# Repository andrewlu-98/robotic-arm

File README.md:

# 6-Axis Robotic Arm (Work in Progress)

An open-source, 6-DOF robotic arm featuring a custom mixed-architecture control board. The system offloads inverse kinematics (ROS 2 / Python) from a host laptop to an onboard Raspberry Pi Pico W analyzing encoder data and generating step signals.

---

## Hardware Overview

### Mechanical
The physical structure consists of a custom 3D printed robotic arm with one meter span. Joints are driven with Nema stepper motors through gear ratios and pulleys, controlling rotation and movement of arm. Motors are to be guided through sensor inputs (limit switches, MT6701) and controlled via Nema Stepper Motors and precise gear ratios.

### Electrical
Electronics consist of a power supply unit (connected to a wall outlet) sent to a PCB that actively controls the robotic arm through signals to the stepper motors and data from encoders and limit switches mounted near the stepper motors on the physical arm.

The printed circuit board handles logic shifting via 74HCT245, limit switch & encoder monitoring, and I2C multiplexing. It houses pin headers for reusability of all boards in case of PCB failure. The board has thermal reliefs on 24V power pours, decoupling, and pull-up resistors for limit switch activation.

---

## System Architecture

### Hardware Stack
*   **Microcontroller:** Raspberry Pi Pico W (RP2040)
*   **Power:** Mean Well LRS-200-24 (24V, 8.8A), DFR0831 Buck Converter (24V to 5V logic)
*   **Actuators:** 
    *   3x STEPPERONLINE Short Body NEMA 17 (Driven via A4988)
    *   1x Leadshine 42CME06 Closed-Loop (Driven via TMC2209)
    *   2x Leadshine iCL57-23 (Integrated Drivers)
*   **Feedback:** MT6701 Magnetic Encoders (I2C) & Leadshine Quadrature Encoders

### Software Stack (In Progress)
*   **Host (Laptop):** ROS 2, Python, MoveIt 2 (Inverse Kinematics, Trajectory Planning, URDF/Xacro modeling).
*   **Firmware (Pico W):** C++ (Pico SDK). 
    *   **Core 0:** Serial communication (micro-ROS/Custom protocol) & Emergency Stop hardware interrupts.
    *   **Core 1:** PID closed-loop feedback processing.
    *   **PIO:** Mathematically precise step/direction pulse generation for 6 axes.

---

## Development Roadmap

- [x] Mechanical Design and Manufacturing
- [x] PCB Design and Manufacturing
- [x] Finalize BOM and Sourcing
- [x] **[Current]** ROS 2 URDF, RViz2, and Gazebo simulation
- [ ] C++ Firmware: Step generation, and analyzing encoder data
- [ ] Communication between laptop and Pico (micro-ROS)
- [ ] Full integration of mechanical, electrical, and software components

---

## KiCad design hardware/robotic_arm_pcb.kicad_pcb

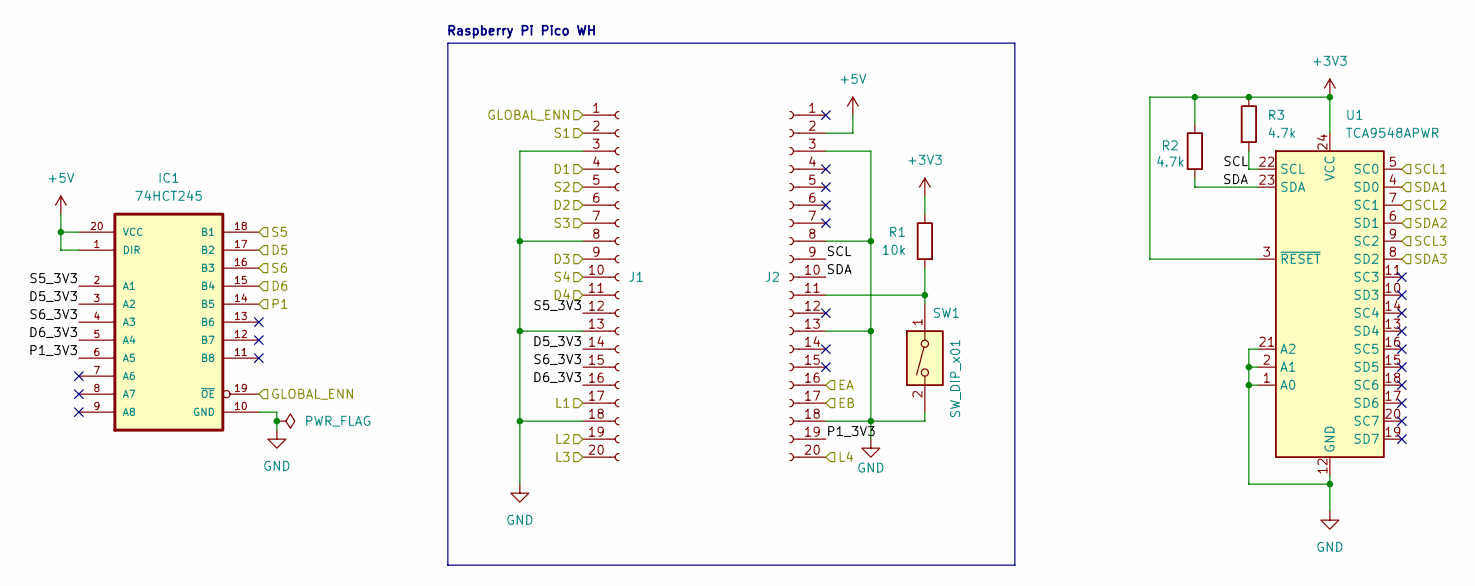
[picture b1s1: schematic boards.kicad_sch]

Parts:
IC1: 74HCT245; MODULE_SN74HCT245N; LCSC C133640
J1, J2: Conn_01x20_Socket; PinSocket_1x20_P2.54mm_Vertical; LCSC C2905423
R1: 10k; R_0805_2012Metric; LCSC C17414
R2, R3: 4.7k; R_0805_2012Metric; LCSC C441984
SW1: SW_DIP_x01; SW_DIP_SPSTx01_Slide_9.78x4.72mm_W7.62mm_P2.54mm; LCSC C501524
U1: TCA9548APWR; TSSOP-24_4.4x7.8mm_P0.65mm; LCSC C130026

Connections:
+3V3: R1.1, R2.1, R3.1, U1.3 (~RESET), U1.24 (VCC); also elsewhere on the board
+5V: IC1.1 (DIR), IC1.20 (VCC), J2.2; also elsewhere on the board
/Boards/D1: J1.4; also elsewhere on the board
/Boards/D2: J1.6; also elsewhere on the board
/Boards/D3: J1.9; also elsewhere on the board
/Boards/D4: J1.11; also elsewhere on the board
/Boards/D5: IC1.17 (B2); also elsewhere on the board
/Boards/D5_3V3: IC1.3 (A2), J1.14
/Boards/D6: IC1.15 (B4); also elsewhere on the board
/Boards/D6_3V3: IC1.5 (A4), J1.16
/Boards/EA: J2.16; also elsewhere on the board
/Boards/EB: J2.17; also elsewhere on the board
/Boards/GLOBAL_ENN: IC1.19 (~OE), J1.1; also elsewhere on the board
/Boards/L1: J1.17; also elsewhere on the board
/Boards/L2: J1.19; also elsewhere on the board
/Boards/L3: J1.20; also elsewhere on the board
/Boards/L4: J2.20; also elsewhere on the board
/Boards/P1: IC1.14 (B5); also elsewhere on the board
/Boards/P1_3V3: IC1.6 (A5), J2.19
/Boards/S1: J1.2; also elsewhere on the board
/Boards/S2: J1.5; also elsewhere on the board
/Boards/S3: J1.7; also elsewhere on the board
/Boards/S4: J1.10; also elsewhere on the board
/Boards/S5: IC1.18 (B1); also elsewhere on the board
/Boards/S5_3V3: IC1.2 (A1), J1.12
/Boards/S6: IC1.16 (B3); also elsewhere on the board
/Boards/S6_3V3: IC1.4 (A3), J1.15
/Boards/SCL: J2.9, R3.2, U1.22 (SCL)
/Boards/SCL1: U1.5 (SC0); also elsewhere on the board
/Boards/SCL2: U1.7 (SC1); also elsewhere on the board
/Boards/SCL3: U1.9 (SC2); also elsewhere on the board
/Boards/SDA: J2.10, R2.2, U1.23 (SDA)
/Boards/SDA1: U1.4 (SD0); also elsewhere on the board
/Boards/SDA2: U1.6 (SD1); also elsewhere on the board
/Boards/SDA3: U1.8 (SD2); also elsewhere on the board
GND: IC1.10 (GND), J1.3, J1.8, J1.13, J1.18, J2.3, J2.8, J2.13, J2.18, SW1.2, U1.1 (A0), U1.2 (A1), U1.12 (GND), U1.21 (A2); also elsewhere on the board
unnamed: J2.11, R1.2, SW1.1

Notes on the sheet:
Raspberry Pi Pico WH

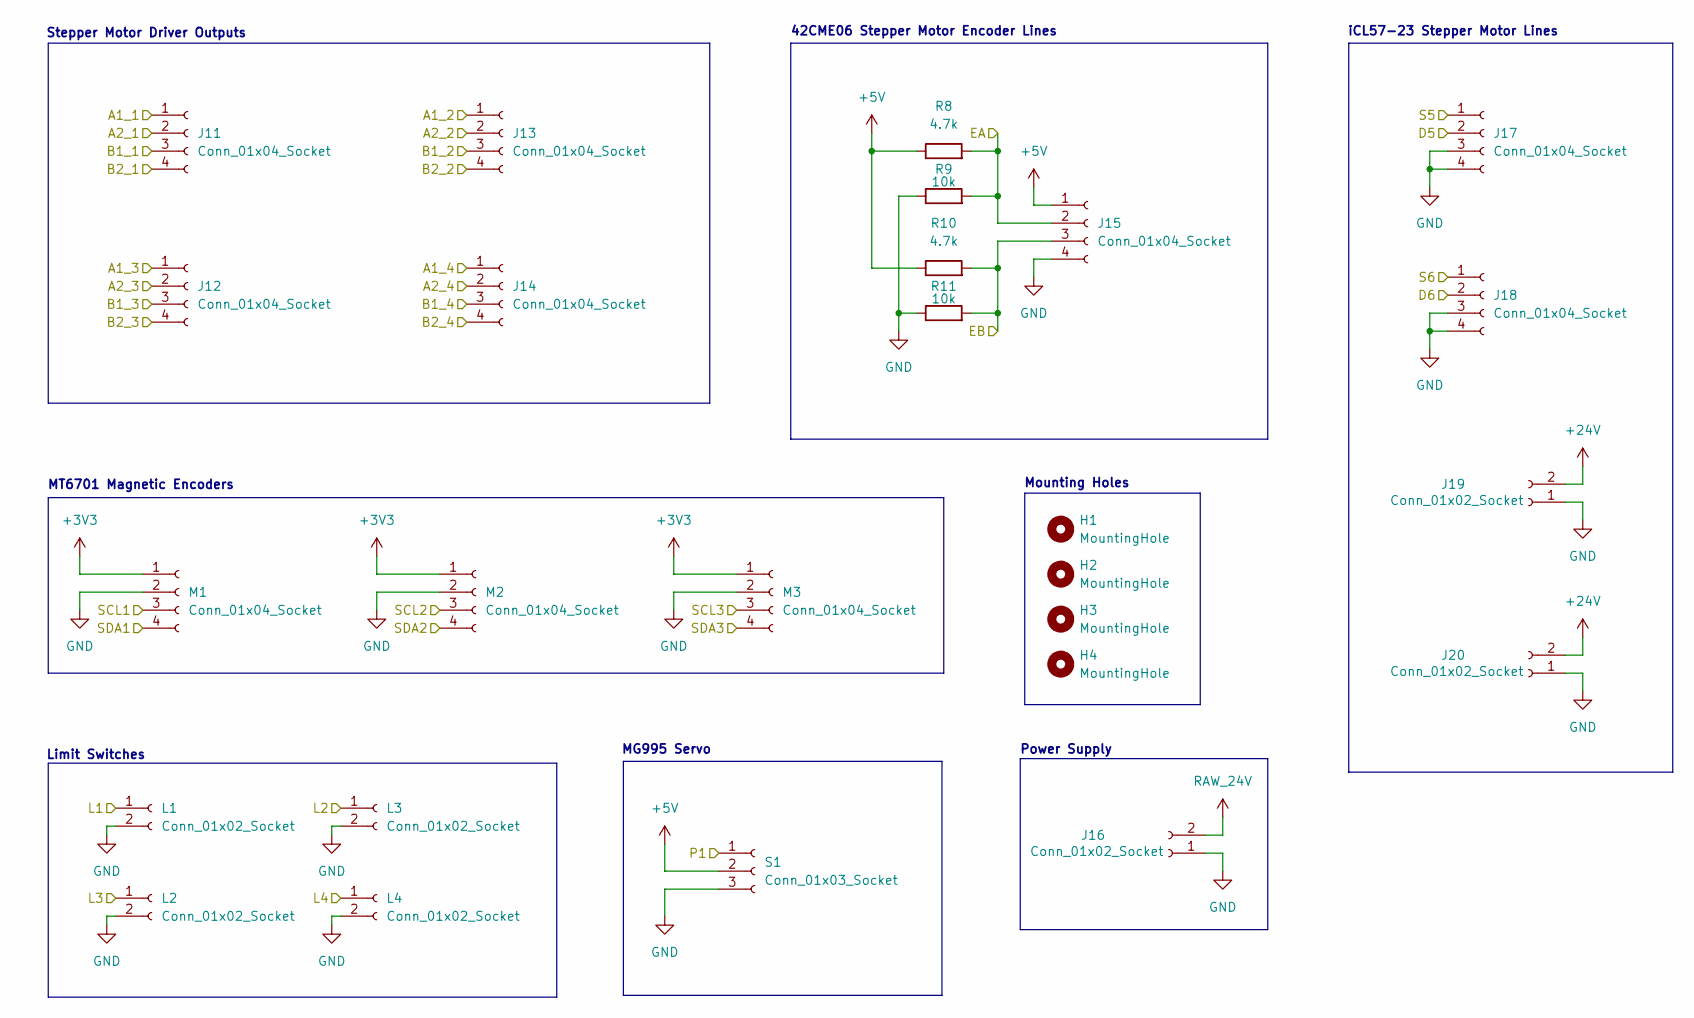
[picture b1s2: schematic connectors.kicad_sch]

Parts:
H1, H2, H3, H4: MountingHole; MountingHole_3.2mm_M3
J11, J12, J13, J14: Conn_01x04_Socket; TerminalBlock_Phoenix_MKDS-1,5-4-5.08_1x04_P5.08mm_Horizont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; LCSC C90087
J15, J17, J18: Conn_01x04_Socket; PinSocket_1x04_P2.54mm_Vertical; LCSC C2718488
J16, J19, J20: Conn_01x02_Socket; TerminalBlock_Phoenix_MKDS-1,5-2-5.08_1x02_P5.08mm_Horizont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; LCSC C474950
L1, L2, L3, L4: Conn_01x02_Socket; PinSocket_1x02_P2.54mm_Vertical; LCSC C49661
M1, M2, M3: Conn_01x04_Socket; PinSocket_1x04_P2.54mm_Vertical; LCSC C2718488
R8, R10: 4.7k; R_0805_2012Metric; LCSC C441984
R9, R11: 10k; R_0805_2012Metric; LCSC C17414
S1: Conn_01x03_Socket; PinSocket_1x03_P2.54mm_Vertical; LCSC C146243

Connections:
+3V3: M1.1, M2.1, M3.1; also elsewhere on the board
+5V: J15.1, R8.1, R10.1, S1.2; also elsewhere on the board
+24V: J19.2, J20.2; also elsewhere on the board
/Boards/D5: J17.2; also elsewhere on the board
/Boards/D6: J18.2; also elsewhere on the board
/Boards/EA: J15.2, R8.2, R9.2; also elsewhere on the board
/Boards/EB: J15.3, R10.2, R11.2; also elsewhere on the board
/Boards/L1: L1.1; also elsewhere on the board
/Boards/L2: L3.1; also elsewhere on the board
/Boards/L3: L2.1; also elsewhere on the board
/Boards/L4: L4.1; also elsewhere on the board
/Boards/P1: S1.1; also elsewhere on the board
/Boards/S5: J17.1; also elsewhere on the board
/Boards/S6: J18.1; also elsewhere on the board
/Boards/SCL1: M1.3; also elsewhere on the board
/Boards/SCL2: M2.3; also elsewhere on the board
/Boards/SCL3: M3.3; also elsewhere on the board
/Boards/SDA1: M1.4; also elsewhere on the board
/Boards/SDA2: M2.4; also elsewhere on the board
/Boards/SDA3: M3.4; also elsewhere on the board
/Connectors/A1_1: J11.1; also elsewhere on the board
/Connectors/A1_2: J13.1; also elsewhere on the board
/Connectors/A1_3: J12.1; also elsewhere on the board
/Connectors/A1_4: J14.1; also elsewhere on the board
/Connectors/A2_1: J11.2; also elsewhere on the board
/Connectors/A2_2: J13.2; also elsewhere on the board
/Connectors/A2_3: J12.2; also elsewhere on the board
/Connectors/A2_4: J14.2; also elsewhere on the board
/Connectors/B1_1: J11.3; also elsewhere on the board
/Connectors/B1_2: J13.3; also elsewhere on the board
/Connectors/B1_3: J12.3; also elsewhere on the board
/Connectors/B1_4: J14.3; also elsewhere on the board
/Connectors/B2_1: J11.4; also elsewhere on the board
/Connectors/B2_2: J13.4; also elsewhere on the board
/Connectors/B2_3: J12.4; also elsewhere on the board
/Connectors/B2_4: J14.4; also elsewhere on the board
GND: J15.4, J16.1, J17.3, J17.4, J18.3, J18.4, J19.1, J20.1, L1.2, L2.2, L3.2, L4.2, M1.2, M2.2, M3.2, R9.1, R11.1, S1.3; also elsewhere on the board
RAW_24V: J16.2; also elsewhere on the board

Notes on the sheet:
Stepper Motor Driver Outputs
Limit Switches
42CME06 Stepper Motor Encoder Lines
Power Supply
iCL57-23 Stepper Motor Lines
MG995 Servo
Mounting Holes
MT6701 Magnetic Encoders

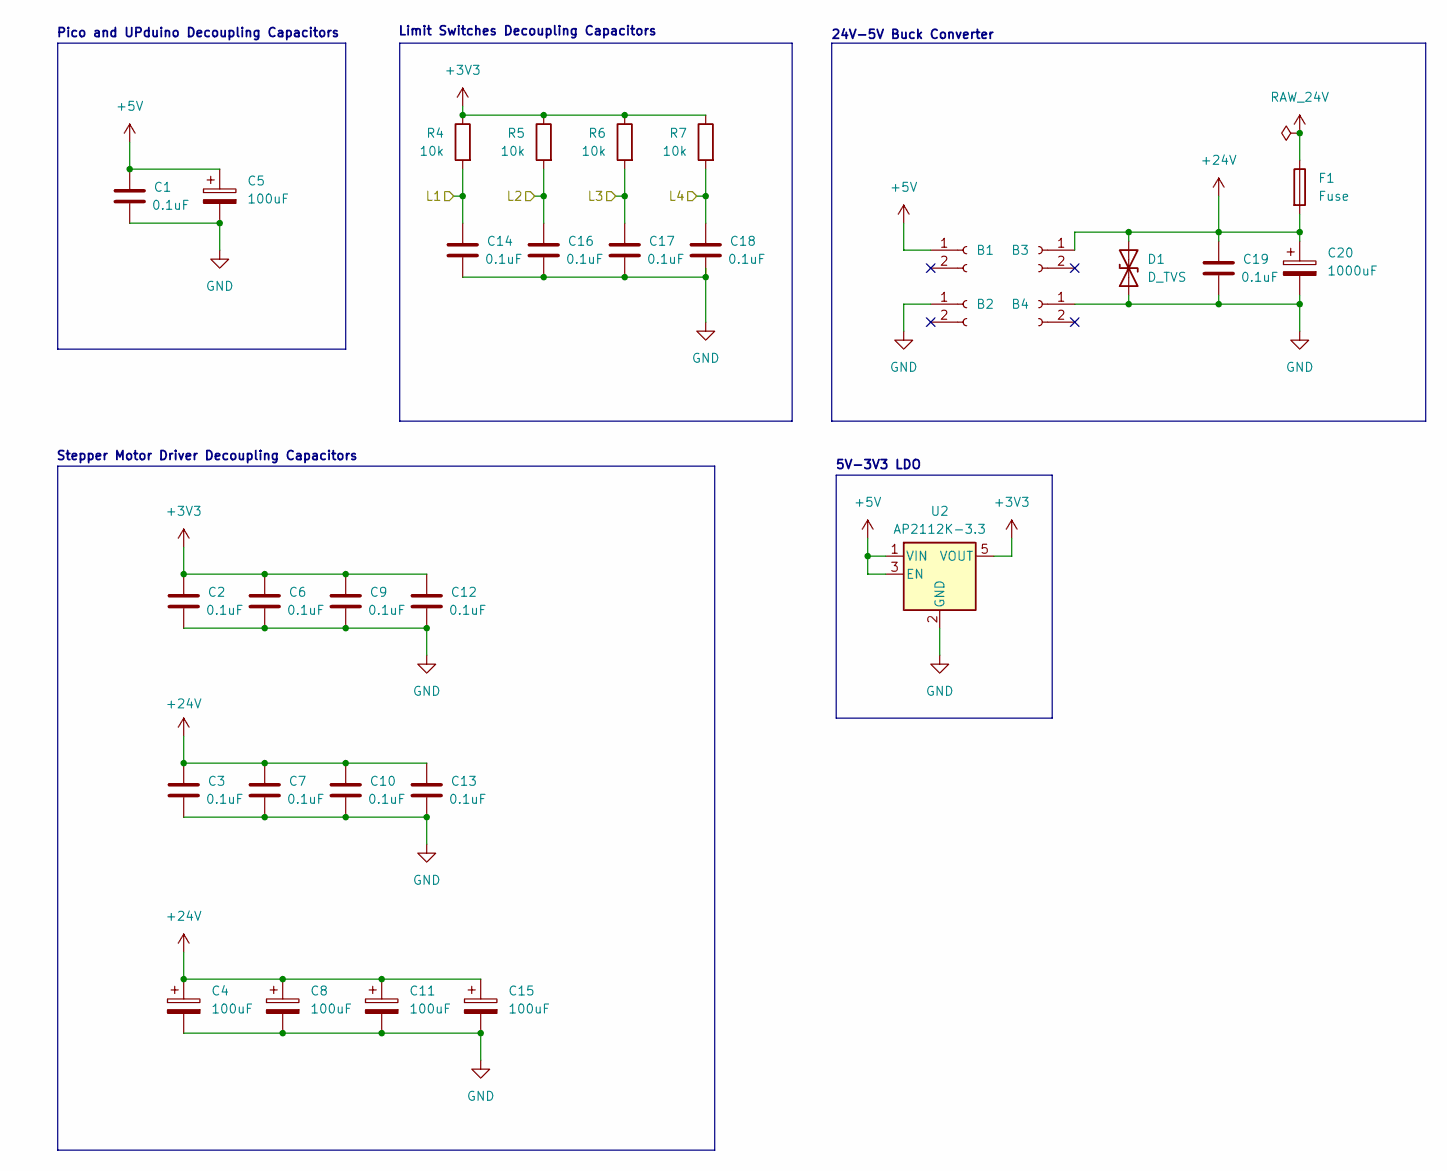
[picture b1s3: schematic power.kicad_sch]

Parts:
B1, B2, B3, B4: Conn_01x02_Socket; PinSocket_1x02_P2.54mm_Vertical; LCSC C49661
C1, C2, C3, C6, C7, C9, C10, C12, C13, C14, C16, C17, C18, C19: 0.1uF; C_0805_2012Metric; LCSC C49678
C4, C5, C8, C11, C15: 100uF; CP_Radial_D6.3mm_P2.50mm; LCSC C2749
C20: 1000uF; CP_Radial_D12.5mm_P5.00mm; LCSC C88743
D1: D_TVS; D_SMB; LCSC C123820
F1: Fuse; Fuseholder_Cylinder-5x20mm_Schurter_0031_8201_Horizontal_Op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; LCSC C3204125
R4, R5, R6, R7: 10k; R_0805_2012Metric; LCSC C17414
U2: AP2112K-3.3; SOT-23-5; LCSC C51118

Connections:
+3V3: C2.1, C6.1, C9.1, C12.1, R4.1, R5.1, R6.1, R7.1, U2.5 (VOUT); also elsewhere on the board
+5V: B1.1 (Pin_1_1), C1.1, C5.1, U2.1 (VIN), U2.3 (EN); also elsewhere on the board
+24V: B3.1 (Pin_1_1), C3.1, C4.1, C7.1, C8.1, C10.1, C11.1, C13.1, C15.1, C19.1, C20.1, D1.2 (A2), F1.2; also elsewhere on the board
/Boards/L1: C14.1, R4.2; also elsewhere on the board
/Boards/L2: C16.1, R5.2; also elsewhere on the board
/Boards/L3: C17.1, R6.2; also elsewhere on the board
/Boards/L4: C18.1, R7.2; also elsewhere on the board
GND: B2.1 (Pin_1_1), B4.1 (Pin_1_1), C1.2, C2.2, C3.2, C4.2, C5.2, C6.2, C7.2, C8.2, C9.2, C10.2, C11.2, C12.2, C13.2, C14.2, C15.2, C16.2, C17.2, C18.2, C19.2, C20.2, D1.1 (A1), U2.2 (GND); also elsewhere on the board
RAW_24V: F1.1; also elsewhere on the board

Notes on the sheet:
Pico and UPduino Decoupling Capacitors
5V-3V3 LDO
Limit Switches Decoupling Capacitors
Stepper Motor Driver Decoupling Capacitors
24V-5V Buck Converter

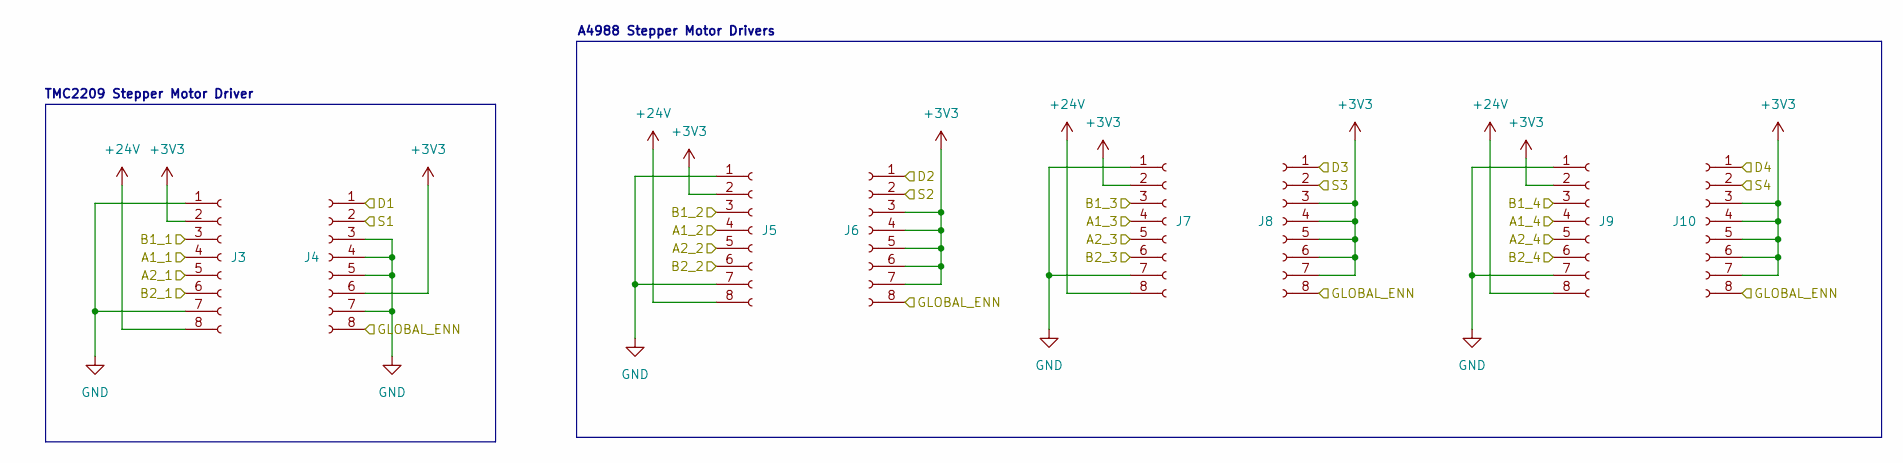
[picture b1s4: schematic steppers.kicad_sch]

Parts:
J3, J4, J5, J6, J7, J8, J9, J10: Conn_01x08_Socket; PinSocket_1x08_P2.54mm_Vertical; LCSC C27438

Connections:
+3V3: J3.2, J4.6, J5.2, J6.3, J6.4, J6.5, J6.6, J6.7, J7.2, J8.3, J8.4, J8.5, J8.6, J8.7, J9.2, J10.3, J10.4, J10.5, J10.6, J10.7; also elsewhere on the board
+24V: J3.8, J5.8, J7.8, J9.8; also elsewhere on the board
/Boards/D1: J4.1; also elsewhere on the board
/Boards/D2: J6.1; also elsewhere on the board
/Boards/D3: J8.1; also elsewhere on the board
/Boards/D4: J10.1; also elsewhere on the board
/Boards/GLOBAL_ENN: J4.8, J6.8, J8.8, J10.8; also elsewhere on the board
/Boards/S1: J4.2; also elsewhere on the board
/Boards/S2: J6.2; also elsewhere on the board
/Boards/S3: J8.2; also elsewhere on the board
/Boards/S4: J10.2; also elsewhere on the board
/Connectors/A1_1: J3.4; also elsewhere on the board
/Connectors/A1_2: J5.4; also elsewhere on the board
/Connectors/A1_3: J7.4; also elsewhere on the board
/Connectors/A1_4: J9.4; also elsewhere on the board
/Connectors/A2_1: J3.5; also elsewhere on the board
/Connectors/A2_2: J5.5; also elsewhere on the board
/Connectors/A2_3: J7.5; also elsewhere on the board
/Connectors/A2_4: J9.5; also elsewhere on the board
/Connectors/B1_1: J3.3; also elsewhere on the board
/Connectors/B1_2: J5.3; also elsewhere on the board
/Connectors/B1_3: J7.3; also elsewhere on the board
/Connectors/B1_4: J9.3; also elsewhere on the board
/Connectors/B2_1: J3.6; also elsewhere on the board
/Connectors/B2_2: J5.6; also elsewhere on the board
/Connectors/B2_3: J7.6; also elsewhere on the board
/Connectors/B2_4: J9.6; also elsewhere on the board
GND: J3.1, J3.7, J4.3, J4.4, J4.5, J4.7, J5.1, J5.7, J7.1, J7.7, J9.1, J9.7; also elsewhere on the board

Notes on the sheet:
TMC2209 Stepper Motor Driver
A4988 Stepper Motor Drivers

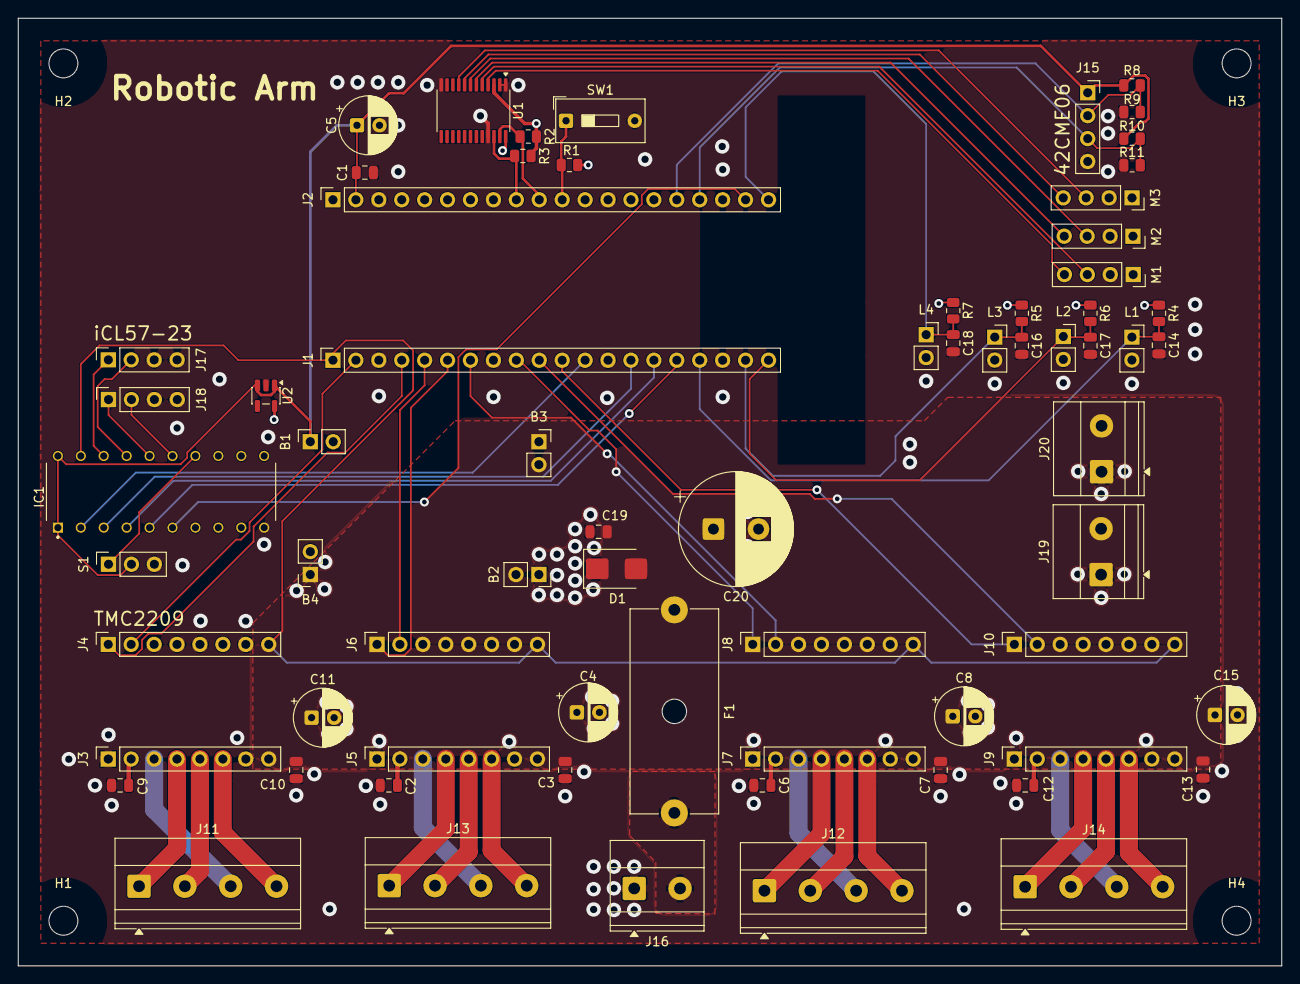
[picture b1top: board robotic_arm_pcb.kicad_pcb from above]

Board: 4 copper layers, 140.0 x 105.0 mm, 73 parts (0 on the bottom side), 55 nets.
